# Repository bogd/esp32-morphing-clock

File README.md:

# esp32-morphing-clock
ESP32 HUB75 Matrix Morphing Clock

A clock based on a HUB75 RGB LED matrix, controlled by an ESP32.

So far, it does the following:
* Displays the current date, time, and day of the week
* Updates the time on startup and periodically, via NTP
* Displays the current outdoor temperature and humidity (received via MQTT - if you want to use this, you will need an MQTT server and a separate temperature sensor publishing to it!)
* Displays the current light levels, read via a TSL2591 I2C light sensor
* Displays the weather forecast for current day (including min/max temperatures), and for the next 4 days
* Can receive OTA updates, triggered via an MQTT message (of course, this also requires an MQTT server :) )

This is very much a work in progress, and it is far from being finished. Things that are planned for the future include:
* Use the current light levels to control the matrix brightness
* Display alerts on-screen (received via MQTT)
* Use the buzzer module to get the user's attention when an alert comes in

You can find the "components" for the project here:
* The full source code is [here](code/)  - requires PlatformIO!
* The schematics for the PCB used is [here](pcb/)
* The drawings for the lasercut plexiglass enclosure are [here](case/)

## Changelog

### Version 0.2
* Added MQTT SSL support (thanks to [Andreas](https://github.com/lefty01)). Disabled by default, since I do not use it when testing
* Implemented weather forecast - clock now displays min/max temperature for today, today's + next 4 days' forecast icons
* Decreased light sensor read interval (interval is now configurable from config.h)
* Added a watchdog timer to automatically reset the unit (sometimes the main thread seems to hang, possibly due to the light sensor read?)

## Thanks

This project would not have been possible without the work of many others, who have been gracious enough to open source their work. Some of the things that I have used when building this:
* The MQTT SSL code contributed by [Andreas](https://github.com/lefty01)
* The PxMatrix library from [2dom](https://github.com/2dom/PxMatrix). Even though this is NOT used in this project (I switched to the DMA library below, for performance reasons), it is the library that got me started on working with HUB75 matrices.
* The ESP32 DMA library for controlling the matrix, from [mrfaptastic](https://github.com/mrfaptastic/ESP32-HUB75-MatrixPanel-I2S-DMA)
* The morphing clock code from [HariFun](https://www.instructables.com/Morphing-Digital-Clock/) (modified to work with mrfaptastic's library instead of pxmatrix)
* The shield schematics from [hallard](https://github.com/hallard/WeMos-Matrix-Shield-DMA), which gave me the confidence to try building my own version of a shield PCB :)

And, of course, all the authors of the various open source libraries (there are already too many to mention :) ).

I also have to mention here [Brian Lough's work](https://www.tindie.com/products/brianlough/esp32-i2s-matrix-shield/) on a shield for the matrix. Even though he decided not to open source the board (he only sells the finished board on tindie), he has been extremely helpful during my initial work on the project. So if you are looking for a simple option for getting the full kit (shield and components, all in one package), take a look at [his tindie page](https://www.tindie.com/products/brianlough/esp32-matrix-shield-mini-32/) .

## License

The ESP32 HUB75 Matrix Morphing Clock is (c) [Bogdan Sass](https://github.com/bogd), licensed with GNU General Public License Version 3.0 (which means, if you use it in a product somewhere, you need to make the source and all your modifications available to the receiver of such product so that they have the freedom to adapt and improve).

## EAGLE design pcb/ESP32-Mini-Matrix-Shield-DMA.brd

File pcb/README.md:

# ESP32 Morphing Clock Shield PCB

## Info

Features:
* 16-wire ribbon cable connection to the RGB matrix
* Mounting holes for securing the shield to the enclosure
* Options for both PTH and SMD (0805/SOD-323) parts for all parts
* Multiple JST-XH (2.54mm) connectors for I2C sensors and for GPIOs (use for push-buttons, for example)
* Exposed JTAG and PROG connectors, for use with debugging/programming via ESP32-Prog (although they are a bit too close together in v0.3 :) )

**WARNING!!** Do not use v0.1 of the boards! I have made several mistakes while designing them (reversed OE/LAT pins on the matrix connector, and put in a WAY too thin power supply trace). As a result, I was unable to get the ESP32 to even boot when connected to these boards.

v0.3 has been tested, and works reliably.

## Components

These are the components that you will need to populate the PCB:
* R1, R2 (I2C pull-up resistors) - 4k7 ohm, PTH or 0805 SMD
* C1,C2,C3 (decoupling capacitor(s)) - either 100uF PTH, or 2x47uF SMD
* D1 (protection diode, prevents the matrix from pulling too much power from your USB port) - any Schottky will work. For example: BAT85 (PTH), or 1N5819 (SOD-323)
* P1 - ribbon cable connector, 2x8 pin
* GND_T/5V_T - 2xScrew terminal blocks, 5.0mm
* power connection - 2.1/5.5mm PCB connector, or **7.62mm** screw terminal block
* I2C and GPIO connectors - JST-XH 2.54mm, 2 and 4-pin 

And, of course, you will need the ESP32 board - it has to be the D1 Mini version:

## Board 

Images of the completed board:

The board with (a minimum of) components soldered on:

Connected to the matrix and the ESP32 module:

## Schematic

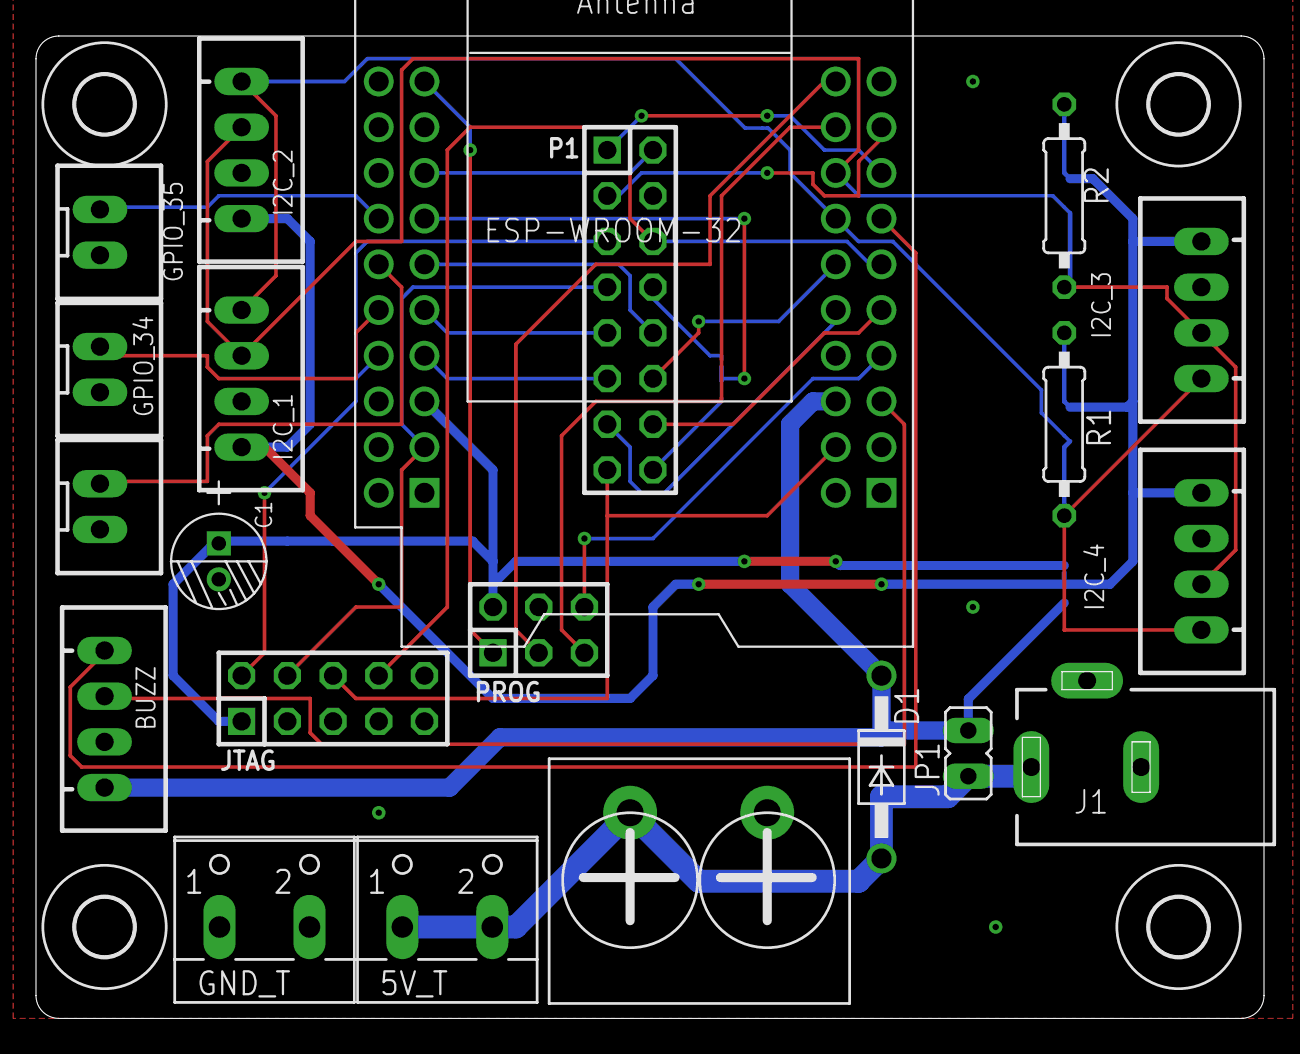
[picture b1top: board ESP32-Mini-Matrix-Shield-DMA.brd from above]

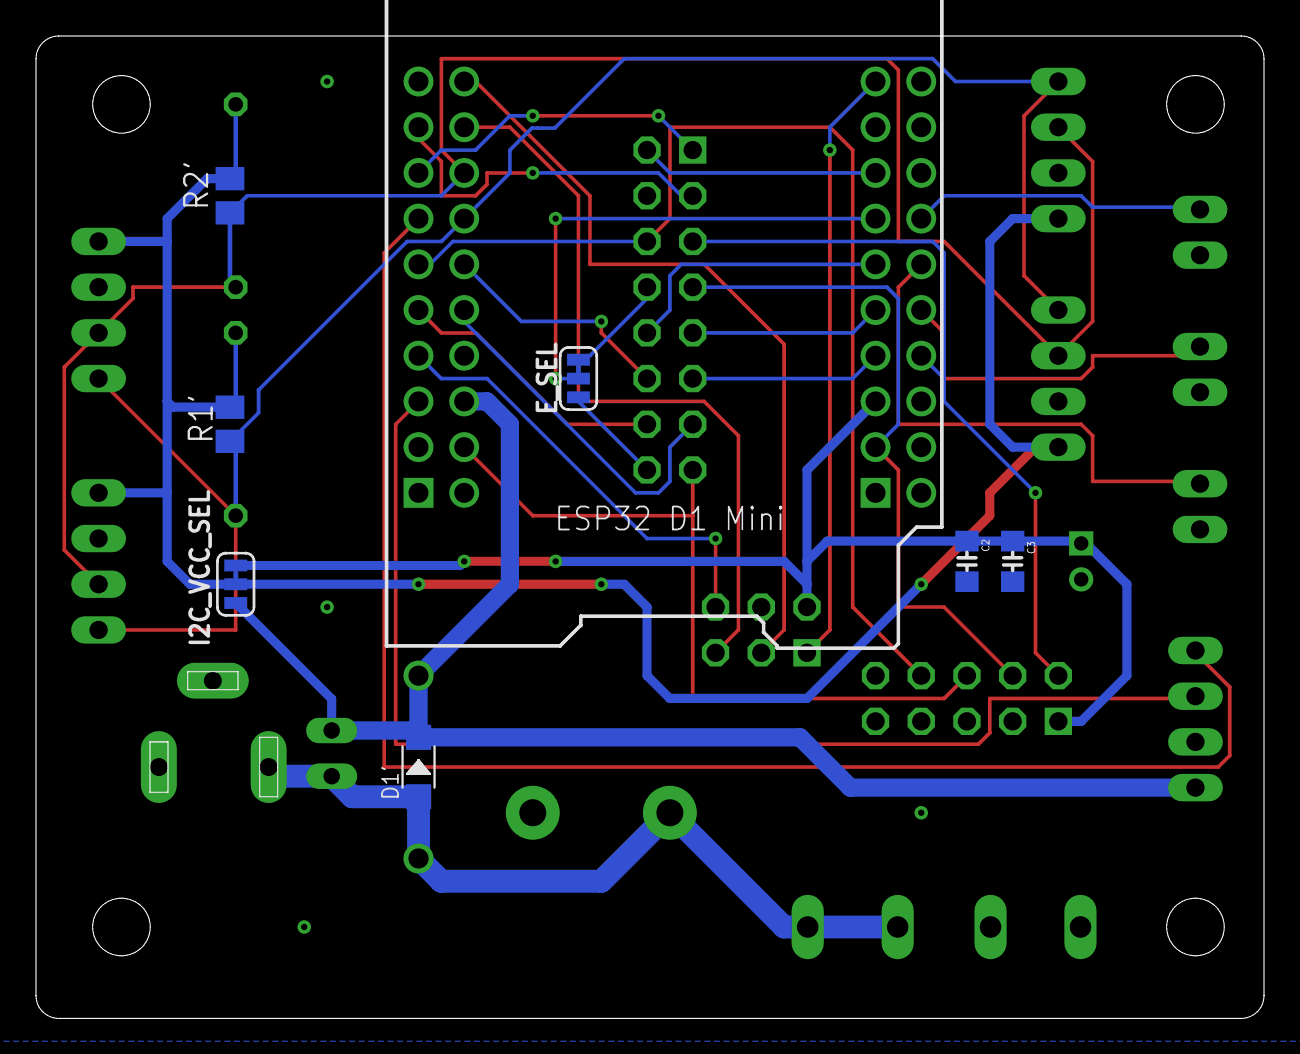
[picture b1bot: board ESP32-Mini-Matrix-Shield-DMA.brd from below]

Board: 2 copper layers, 68.2 x 54.6 mm, 32 parts (7 on the bottom side), 32 nets.

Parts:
5V_T: 5V; W237-102
BUZZ: BUZZER; JST-XH-04-PACKAGE-LONG-PAD
C1: 100uF; PC-D5.3MM
C2, C3: 47 uF; 0805-CAP-LARGEPADS
D1: Schottky; DO41-10
D1': 20V-1A; SOD-123
ESP32_D1_MINI: ESP32 D1 Mini; MH-ET_ESP32_D1_MINI
E_SEL: SMT-JUMPER_3_1-NC_TRACE_SILK
GND_T: GND; W237-102
GPIO_33: GPIO_33; JST-XH-02-PACKAGE-LONG-PAD
GPIO_34: GPIO_34; JST-XH-02-PACKAGE-LONG-PAD
GPIO_35: GPIO_35; JST-XH-02-PACKAGE-LONG-PAD
H1, H2, H3, H4: MOUNT-HOLE3.2; 3,2
I2C_1: I2C_1; JST-XH-04-PACKAGE-LONG-PAD
I2C_2: I2C_2; JST-XH-04-PACKAGE-LONG-PAD
I2C_3: I2C_3; JST-XH-04-PACKAGE-LONG-PAD
I2C_4: I2C_4; JST-XH-04-PACKAGE-LONG-PAD
I2C_VCC_SEL: SMT-JUMPER_3_1-NC_TRACE_SILK
J1: 5.5/2.1mm; DCJ0303
JP1: Diode Bypass; JP1
JTAG: M-2X05-DIL-100; DIL-100-2X05
P1: M-2X08-DIL-100; DIL-100-2X08
PROG: M-2X03-DIL-100; DIL-100-2X03
R1, R2: 4K7; 0207/10
R1', R2': 4K7; M0805
ST_01: ST_01; CON-TERM-7.62

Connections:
3V3: C1.+, C2.1, C3.1, ESP32_D1_MINI.3V3, I2C_VCC_SEL.3, JTAG.1, PROG.2
5V: BUZZ.4, D1.C, D1'.-, ESP32_D1_MINI.VCC, I2C_VCC_SEL.1, JP1.2
5V_EXT: 5V_T.1, 5V_T.2, D1.A, D1'.+, J1.1, JP1.1, ST_01.P$1
A: ESP32_D1_MINI.IO23, P1.9
B: ESP32_D1_MINI.IO19, P1.10
B1: ESP32_D1_MINI.IO27, P1.3
C: ESP32_D1_MINI.IO5, P1.11
CK: ESP32_D1_MINI.IO16, P1.13
D: ESP32_D1_MINI.IO17, P1.12
E: ESP32_D1_MINI.IO18, E_SEL.2
ESP_IO0: ESP32_D1_MINI.IO0, PROG.6
ESP_RXD: ESP32_D1_MINI.RXD, PROG.5
ESP_TXD: ESP32_D1_MINI.TXD, PROG.3
E_P08: E_SEL.3, P1.8
E_P16: E_SEL.1, P1.16
G1: ESP32_D1_MINI.IO26, P1.2
GND: BUZZ.3, C1.-, C2.2, C3.2, ESP32_D1_MINI.GND, ESP32_D1_MINI.GND2, ESP32_D1_MINI.GND3, GND_T.1, GND_T.2, GPIO_33.2, GPIO_34.2, GPIO_35.2, I2C_1.3, I2C_2.3, I2C_3.3, I2C_4.3, J1.2, J1.3, JTAG.3, JTAG.5, JTAG.7, JTAG.9, P1.4, PROG.4, ST_01.P$2
I2C_VCC: I2C_1.4, I2C_2.4, I2C_3.4, I2C_4.4, I2C_VCC_SEL.2, R1.2, R1'.1, R2.2, R2'.2
IO2: BUZZ.2, ESP32_D1_MINI.IO2
IO32: BUZZ.1, ESP32_D1_MINI.IO32
IO33: ESP32_D1_MINI.IO33, GPIO_33.1
IO34: ESP32_D1_MINI.IO34, GPIO_34.1
IO35: ESP32_D1_MINI.IO35, GPIO_35.1
LS: ESP32_D1_MINI.IO4, P1.14
R1: ESP32_D1_MINI.IO25, P1.1
RST: ESP32_D1_MINI.RST, PROG.1
SCL: ESP32_D1_MINI.IO22, I2C_1.2, I2C_2.2, I2C_3.2, I2C_4.2, R2.1, R2'.1
SDA: ESP32_D1_MINI.IO21, I2C_1.1, I2C_2.1, I2C_3.1, I2C_4.1, R1.1, R1'.2
TCK: ESP32_D1_MINI.TCK, JTAG.4, P1.7
TDI: ESP32_D1_MINI.TDI, JTAG.8, P1.6
TDO: ESP32_D1_MINI.TD0, JTAG.6, P1.15
TMS: ESP32_D1_MINI.TMS, JTAG.2, P1.5

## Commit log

2021-04-21 Photos
2021-04-21 Added case designs
2021-04-21 Case designs readme
2021-04-21 Added PCBs
2021-04-21 Added PCB Schematic
2021-04-21 Added Gerber photos
2021-06-12 Updated PCB to v0.3
2021-06-12 Added PCB photos
2021-06-12 PCB Photos resize
2021-06-12 PCB readme update
2021-06-12 Code readme update
2021-06-15 adding mqtt ssl support
2021-06-16 revert to 'official' LED MATRIX PANEL DMA Display lib
2021-11-09 Readme update
2021-11-09 Default to SSL off for MQTT
2021-11-09 Fix SSL deactivation
2021-11-09 Revert light sensor ticker
2021-11-11 Add weather forecast - accuweather

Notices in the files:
parts and their libraries:
con-headers-jp: Copyright (C) 2008, Bob Starr
SparkFun-Jumpers: Licensing: Creative Commons ShareAlike 4.0 International - https://creativecommons.org/licenses/by-sa/4.0
